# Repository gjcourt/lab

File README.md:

<!-- readme-type: content -->

# lab

A curated list of 140 multidisciplinary engineering and skill-building projects

Picking a next project to learn on tends to default to whatever's easiest, not to whatever actually
builds a skill that's missing. `lab` (formerly `brainstorm`) tracks 140 project briefs spanning
software, hardware, woodworking, finance, and music, each one scoped and leveled against existing
skills (Go, Kubernetes, Docker) so the next pick is deliberate rather than convenient. It's a
personal planning catalog, not a set of finished write-ups — most entries are still `Not Started`.

**Status:** active — 140 briefs (1 done, 17 in progress), last content update 2026-10-08; the
espresso profiling build is installed on the machine and its controller app, Vibrato, runs in the
homelab (see [`06-coffee-espresso/AGENTS.md`](06-coffee-espresso/AGENTS.md)).

## Layout

Each directory holds one Markdown file per project plus a `projects.md` index; three also carry a
`_reference/` directory with as-built notes for the work that's actually underway.

```text
01-audio-midi/          22 projects — DSP, custom controllers, and audio hardware
02-woodworking/         15 projects — functional furniture, speaker cabinets, homelab enclosures
03-homelab-automation/  43 projects — eBPF, K8s operators, ESP32 sensors, and infrastructure
04-finance-analysis/    16 projects — EDGAR parsing, DCF modeling, personal finance tracking
05-piano/               15 projects — classical repertoire tools, jazz theory, improvisation
06-coffee-espresso/     19 projects — Lucca A53 profiling, leva! firmware, sensor integration
07-cross-disciplinary/  10 projects — projects blending multiple categories
```

## Conventions

Each project is one file, `NN-NNN-slug.md`, inside its category directory, where `NN` matches the
directory prefix. Every file starts with YAML frontmatter:

```yaml
---
title: 'ESP32 I2S DAC Streamer'
number: '01-001'
category: 'audio-midi'
difficulty: 'Medium'
time_commitment: '1-4 weeks'
target_skills: 'C++, ESP-IDF, I2S, Audio Streaming'
status: 'Not Started'
depends_on: # optional
  - hardware/esp32
---
```

`difficulty` is `Easy` (1-2 days, builds on existing skills), `Medium` (1-4 weeks, combines
disciplines or introduces new concepts), or `Hard` (months, stretches into low-level domains such as
C/C++, RTOS, or advanced finance/music theory). `status` moves from `Not Started` through
`In Progress` to `Done`, or ends at `Cancelled` when a project is dropped. `depends_on` points at a
prerequisite — another project's `NN-NNN`, or a resource reference like `hardware/esp32`. Every file
also needs an `## Exit Criteria` section.

To add a project, create the file with this frontmatter in the right category directory and update
that category's `projects.md` count. To renumber prefixes after reordering, run
`python update_prefixes.py`. See [`AGENTS.md`](AGENTS.md) for the validation commands CI runs on
every change.

## License

No licence file yet.

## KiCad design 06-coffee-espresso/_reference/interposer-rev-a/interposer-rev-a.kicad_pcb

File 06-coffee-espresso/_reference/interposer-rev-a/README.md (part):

# Unified ESP32 interposer, rev A: schematic

The schematic for [06-014](../../06-014-unified-esp32-interposer-board.md), drawn before George's
measurements M1–M10 came in and updated on 2026-11-08 with the ones he took that day (bench page
Tests 28–37, one per M; cited as **Test n**). The design of record is the
[rev A plan](../../../docs/plans/2026-10-27-unified-esp32-interposer-rev-a-plan.md) (cited as **plan
§n**). The 06-015 flow tap it absorbs is in [`../flow-tap-pcb/`](../flow-tap-pcb/README.md).

**Status (2026-11-08): schematic as data, ERC-clean; draft layout, DRC-clean, not ready to order**
(see [Layout](#layout-draft-2026-11-08) and its
[not ready to order until](#not-ready-to-order-until) list). M1, M6, M7 and M9 are closed; M2 is
closed to "EXCON 2547, probable" (caliper check pending); M3 has its resistance half and George's
front-end decision but no live node voltages; M10 has the mount sites but no cable lengths. Nothing
here is a guess. Every value that waits on a measurement is listed in
[Placeholders](#placeholders-what-closes-each-one), and every part number comes from a datasheet or
a JLCPCB part page read on 2026-10-28 (no new LCSC numbers were added on 2026-11-08).

| File                                                 | What it is                                                                                                   |
| ---------------------------------------------------- | ------------------------------------------------------------------------------------------------------------ |
| [`circuit.py`](circuit.py)                           | **Single source of truth.** Parts, nets, NC pads, GPIO map, placeholders. Importable by a future generator.  |
| [`check_circuit.py`](check_circuit.py)               | ERC-style checker (11 checks). Exit 0 = pass.                                                                |
| [`footprints/`](footprints/)                         | The 26 footprints `circuit.py` names (24 KiCad 9 library, 2 EXCON authored) + 2 layout-only (hole, test pad) |
| [`gen_excon_footprints.py`](gen_excon_footprints.py) | Writes `EXCON_2547-02_WV` / `-04_WV` from EXCON drawing C2547WV rev E. Plain Python.                         |
| [`generate_pcb.py`](generate_pcb.py)                 | Layout generator (KiCad 9 `pcbnew` API): reads `circuit.py`, writes the board, BOM and CPL.                  |
| `interposer-rev-a.kicad_*`, `fp-lib-table`           | The generated KiCad project (board, netclasses, custom DRC rule, library table pointing at `footprints/`).   |
| [`routing/`](routing/)                               | The Freerouting session the board is built from (committed, so regeneration doesn't need the router).        |
| [`fab/`](fab/)                                       | Gerber + drill zip, JLC BOM + CPL, assembly drawing (PDF), top/bottom renders, DRC report.                   |

```sh
cd 06-coffee-espresso/_reference/interposer-rev-a
python3 circuit.py              # part / net summary per function block
python3 check_circuit.py -v     # ERC; -v also prints the GPIO map
```

Output today: `116 parts (74 fitted, 42 DNP), 86 nets` and `ALL 11 CHECKS PASS`. Plain Python 3, no
dependencies. The checker reads pad names straight out of the vendored `.kicad_mod` files, so a typo
in a pin number fails C1.

**No KiCad schematic (`.kicad_sch`) in this rev.** kiutils can write one, but every one of the 105
parts would need a library symbol placed and wired or labelled by hand-written coordinates, and
`kicad-cli` has no headless netlist import to validate a `.net` file against. That is hours for a
drawing that adds nothing `circuit.py` + the checker don't already enforce. The layout generator
should read `circuit.py` directly (as 06-015's `generate_pcb.py` hard-codes its nets today), and DRC
on the generated board is the KiCad-side validation.

## What the checker enforces

| #   | Rule                                                                                                                                                                                           | Source                      |
| --- | ---------------------------------------------------------------------------------------------------------------------------------------------------------------------------------------------- | --------------------------- |
| C1  | Every part has a vendored footprint; every `REF.pad` named exists in it                                                                                                                        | KiCad 9 library             |
| C2  | Every footprint pad is on a net or listed in `NC` with a reason                                                                                                                                | —                           |
| C3  | Every net ≥ 2 pins; no pin on two nets                                                                                                                                                         | —                           |
| C4  | GICAR meter supply (`N_PLUS`; ~3.3 V measured, Test 36) touches only `J1.2` / `J2.2`                                                                                                           | 06-015, plan §3.4           |
| C5  | ito 5 V (`V5_ITO`, `ITO_EXP_5V`) never meets `+3V3` / `+5V` / `VBUS`, directly or through any R, C, D, jumper or switch; U1 on ito 5 V, U2 on 3V3                                              | plan §3.4                   |
| C6  | Each GPIO used once and matches the GPIO table; no strapping, octal-PSRAM, UART0 or non-existent pin; USB only on GPIO19/20; analog nets on ADC1                                               | ESP32-S3-WROOM-1 DS v1.8    |
| C7  | `SB` / `SL` probe lines touch only the pass-through connectors and the series coupling cap; the aux pins are pure pass-through                                                                 | plan §3.3                   |
| C8  | `S1` / `S2` feeds touch only the pass-through connectors and one series R into a follower; the follower input has only a BAV99 to +5V / GND; the divider holds the ADS input under VDD + 0.3 V | plan §3.2, SBAS444E         |
| C9  | `ENC` lines touch only connectors, FET drains (source on GND, gate pulled down) and LVC inputs: pull-low only, never driven high. J14.1 NC, J15.1 GND                                          | plan §3.5, Test 33          |
| C10 | IC power pins on the intended rails                                                                                                                                                            | each datasheet's pin table  |
| C11 | M9 tap: U13's line pins, its RX output and the passive path reach M9 / GPIO38 only through DNP links; DIN1 has its pull-up                                                                     | George 2026-11-08, SLLS410O |

The checker was mutation-tested: putting a part on `N_PLUS`, a resistor on `SB_PROBE`, a pull-up on
`ENC_A`, GPIO3 on a signal, or `R39` from `V5_ITO` to 3V3 each fails the right check. On 2026-11-08:
a part on `S1_FEED`, a clamp off its rail, and a GND on `J14.1` each fail too.

## Blocks

Pass-through copper is drawn `═══`. Every machine signal goes in on one connector and straight out
on its mate. Only `ENC` can pull low (plan §2 design invariant).

### F0 power, ESP32, USB

```text
 J4 XH-2 (5V in, our choice: 1 = +5V, 2 = GND) ──────────────┬── +5V ──┬── U6 VDD (NTC followers)
                                                             │         │
 J5 USB-C ── VBUS ──►|── D1 SS34 (VBUS → +5V only) ──────────┘   C3 10µ│
   CC1 ── R1 5k1 ── GND     CC2 ── R2 5k1 ── GND                       │
   D+ (A6,B6) ══ U3 USBLC6-2SC6 (1/6) ══ GPIO20                 U4 AMS1117-3.3 (VIN 3, GND 1, VOUT 2/tab)
   D- (A7,B7) ══ U3 (3/4) ═════════════ GPIO19                         │
   U3.5 VBUS, U3.2 GND                                         +3V3 ──┴── C4 22µ ── U5.2 3V3 (C5 22µ + C6 100n at pin)
 U5 ESP32-S3-WROOM-1-N8:  EN ── R3 10k ── 3V3, C7 1µ ── GND, SW1 ── GND   (DS v1.8 §9: R = 10k, C = 1µF)
                          GPIO0 ── R4 10k ── 3V3, SW2 (BOOT) ── GND
```

- **Never plug USB in while the machine is plugged in** (plan §3.1). D1 only stops the 5 V PSU
  back-feeding a USB host. It is not isolation.
- **The board's GND is chassis earth once installed.** The control board's GND is isolated from
  mains (Test 28: GND to N and to F open unplugged; GND to PE 2 mV AC, 0 V DC powered; PS1 is a
  Lauma SMR30.10, Class II), but it is bonded to the chassis through M3 pin 4, the steam-level
  return to the boiler body (Test 30: GND to the earth screw beeps with M3 plugged in, not with it
  out). So flash an installed board from a grounded or battery-powered laptop.
- **USB headroom:** AMS1117 dropout is 1.3 V max at 0.8 A, so it wants ≥ 4.6 V in. USB through D1
  can sit just under that. Flashing works; Wi-Fi TX peaks on USB power may brown out. Use J4 for
  bench tests T2+.

### F1 / F2 `S1` / `S2` NTC taps (one follower per feed)

The control board's sensor headers (Test 29, George's trace on his v.05.01 board): **M2** 2-pin =
steam NTC (`S1`), 1 GND, 2 feed. **M3** 4-pin = 1 GND, 2 group NTC feed (`S2`), 3 steam-boiler level
probe (`SB`), 4 GND (the level return, wired to the boiler body). So `S2` and `SB` share one plug,
and J8/J9 carry both.

```text
 J6.2 (S1 steam probe) ═══════ S1_FEED ═══════ J7.2 (→ control board M2.2)
 J6.1 / J7.1 = GND (Test 30: 0.2 Ω to M6 pin 3)  ── tied to the board GND
                                │
                               R5 1M                       (George 2026-11-08: "1 MΩ series")
                                │  S1_IN ── D2 BAV99 to +5V / GND
                       U6A MCP6004 follower (IN+ 3, IN- 2 = OUT 1), VDD = +5V
                                │  S1_BUF
                               R9 10k ── S1_ADC ── R13 5.1k ── GND, C9 100n ── GND
                                │
                           U7 ADS1115 AIN0          S2: J8.2/J9.2, R6, D3, U6B, R10/R14, C10 → AIN1
 U7: VDD 3V3 (C13 100n), ADDR = GND → 0x48, AIN2/AIN3 = GND (unused), ALERT/RDY → R21 10k ── 3V3, GPIO10
 U6C / U6D unused: OUT tied to IN-, IN+ at GND
```

- **George's decisions (2026-11-08).** First: "Measure 0–5.5 V, survive 24 V", a high-impedance
  buffered input with series R plus clamp diodes so up to ~24 V can't damage it, without loading the
  probe (the control board must read the same temperature). Then, answering the two questions this
  raised: **"1 MΩ series"** and **"Accept 0–5.0 V"**.
- **Only the feed is buffered.** Test 30 found pin 1 of each probe header at GND (0.2 Ω) and pin 2
  the feed, so the second follower per probe that rev A drew "in case the GND pin is the other one"
  is gone, and the NTC GND pins join the board GND.
- **Range: 0 to ~5.0 V.** U6 stays on +5V. The MCP6004 is rail-to-rail: its input range ends at
  VDD + 0.3 V and its output at VDD − 25 mV (DS20001733L), so it reads 0 to ~5.0 V. That covers the
  1.5–4.7 V estimate below. Revisit in rev B if the live measurement shows the node near 5 V.
- **Divider after the follower, unchanged.** R9/R13 = 10k/5.1k = 0.338: 5.0 V at the node is 1.69 V
  at the ADS, 83 % of the ±2.048 V FSR, ~185 µV per code at the node. A closer ratio would need a
  new resistor value for less than one bit, so it stays. The follower output can't exceed +5V, so
  the ADS pin stays under VDD + 0.3 V (SBAS444E abs max; checker C8). The divider loads the op-amp,
  never the node.
- **Series R = 1 MΩ.** A 24 V fault pushes (24 − 5.3) V / 1 MΩ = 19 µA into D2 and the op-amp input
  diodes, against the MCP6004's ±2 mA input-pin rating (checker C8 recomputes this). With the
  interposer **unpowered** and the machine on, the feed reaches the dead +5V rail through 1 MΩ and
  the clamp: with the 5 V / 15 kΩ model at 94 °C that is ~1.7 µA, ~12 mV at the group node, about
  0.3 °C at the control board (100 kΩ would have been ~3 °C). **Test T4 runs with the interposer
  powered and unpowered.**
- **D2/D3 fitted, with a cost to watch.** BAV99 leakage is ≤ 25 nA at 20 V (Diodes ds12007). Through
  1 MΩ that is ≤ 25 mV worst case at the follower (~0.6 °C at 94 °C), and ≤ 0.4 mV at the node
  through the ~15 kΩ feed, so it costs reading accuracy, not control-board accuracy. If T3 shows it
  matters, D2/D3 can go DNP: the op-amp's own input diodes and 1 MΩ still hold a 24 V fault to 19
  µA.
- **Node estimate (Test 30, not yet measured live):** feed pin to GND reads 15 kΩ (M3) and 16.5 kΩ
  (M2) on the unpowered board, so assuming 5 V through ~15 kΩ: group ~4.7 V cold and ~2.4 V at 94
  °C, steam ~4.6 V cold and ~1.5 V at 6.8 kΩ. The live check waits for an EXCON extension lead.
- **Curves (firmware, Test 30):** group 249 kΩ at 21 °C and 13.3 kΩ at 94 °C, so β ≈ 4340 K, R25 ≈
  205 kΩ. Steam 201.7 kΩ at 21 °C and 6.8 kΩ hot at an unknown temperature: it needs a second known
  point.

### F3 / F4 `SB` / `SL` level taps (pass-through + DNP AC front-end)

```text
 J8.3 (SB probe, M3 pin 3) ═════ SB_PROBE ═════ J9.3     J8.4 ═════ SB_AUX (level return) ═════ J9.4
                           │                                (pure pass-through: not tied to our GND)
                        C14 (DNP, series coupling C; value + voltage TBD at M4)
                           │  SB_AC
                        R22 100k (DNP)
                           │  SB_FE ── R24 1M ── 3V3, R26 1M ── GND (DNP mid-rail bias)
                           │         D6 BAV99 (DNP) to 3V3 / GND
                         GPIO1 (ADC1_CH0)          SL: J12/J13 (M10), C15, R23, R25, R27, D7 → GPIO2 (ADC1_CH1)
```

- The probe line touches **only** the connectors and C14 (checker C7). The bias sits on our side of
  the capacitor, so no DC ever reaches the probe (plan §3.3).
- The level return (M3 pin 4) is GND on the control board (0.9 Ω, Test 30) and runs to the boiler
  body. It is kept pure pass-through here so the probe's current never runs through our ground
  plane.
- Firmware samples the AC amplitude on ADC1. ADC1 is used because ADC2 can't run alongside Wi-Fi
  (ESP32-S3 Series DS v2.2).
- Everything after the connectors is DNP until M4/M5 (Tests 31/32 not done). `SL` is M10, a 2-pin
  EXCON header (Test 29); which pin is signal and which is return is unknown, so pin 1 is drawn as
  the tapped line and pin 2 is passed through and touches nothing else.

### F5 flow: 06-015 circuit + ESP32 buffer

```text
 J1 GICAR (EXCON 2547-4)                           J2 to control board M6 (EXCON 2547-4)
   1 key-blank                                       1 key-blank
   2 + ~3.3V ══════════ N_PLUS ═══════════════════   2     (J1.2 ↔ J2.2 ONLY; checker C4)
   3 GND    ═══════════ GND ══════════════════════   3
   4 o      ═══════════ N_O ══════════════════════   4
                         ├── U1 74LVC1G17 @ ito 5V (VCC 5 = J3.3 V5_ITO, C1 100n) ── Y 4 ── J3.2 → ito IMPULSE
                         └── U2 74LVC1G17 @ 3V3 (C2 100n) ── Y 4 ── FLOW_3V3 ── GPIO11 (pulse_counter)
 J3 to ito (XH-3): 1 GND, 2 OUT, 3 +5V (ito's)
```

- J3/U1/C1 and the net names are 06-015's, unchanged. **J1/J2 change family:** M6 is the same black
  EXCON 2547 header as the sensor headers (Test 29), not JST XH, so the 06-015 XH pair does not mate
  with this machine.
- **The meter supply is ~3.3 V here, not 14.3 V** (Test 36, meter unplugged: P2→P3 3.3 V, P4→P3 4.9
  V, P2→P4 1.62 V; P2 red, P3 black, P4 white, P1 the blank key). The 14.3 V figure came from a
  forum thread, never this machine. Everything on M6 is ≤ 5 V. The pass-through-only rule (checker
  C4) stays: it is the meter's own supply. The loaded supply voltage (meter connected) waits for an
  EXCON extension lead.
- **The plan's "confirm at layout" is closed:** SN74LVC1G17 input range is 0–5.5 V at any VCC
  (SCES351Y, recommended operating conditions), so U2 takes the 4.9 V `o` while powered from 3.3 V.
  Ioff keeps both buffers from loading `o` when their supply is off.
- ito's 5 V (`V5_ITO`) and our `+3V3` / `+5V` share only GND (checker C5).

### F6 ito `ENC` interposer (3 lines: SW, A, B)

```text
 J14 KK-4 (encoder cable)  1 empty (NC)          1 GND ═══ J15 KK-4 (to ito ENC)
                           2 SW  ═══ ENC_SW ═══ 2 ── Q3 drain │ U10 A
                           3 A   ═══ ENC_A ════ 3 ── Q1 drain │ U8 A
                           4 B   ═══ ENC_B ════ 4 ── Q2 drain │ U9 A
 inject:  GPIO4/5/6 ── R28-30 1k ── gate Q1-3 AO3400A (source GND) ; gate ── R31-33 100k ── GND
 read:    U8/U9/U10 74LVC1G17 @ 3V3 (C16-18 100n), Y → GPIO7 / GPIO15 / GPIO16
```

- **Three lines.** The encoder sits on the display board (V1.3), and its cable carries only SW / A /
  B in holes 2 / 3 / 4; hole 1 is empty, because the display board gets GND over the SPI cable (Test
  33). Each line passes a 4.7 kΩ series resistor on the display board (R1–R3, with C5–C7 on the
  encoder side). ito's ENC pin 1 is GND, so J15.1 carries our GND to ito as the FETs' return, and
  J14.1 is NC (checker C9). The order matches the ito manual (p.63) and the KK 254 2.54 mm family
  (Test 33: ~7.7 mm across 4 pins).
- **Idle high, pull-low only** (Test 34, in the machine): SW, A and B rest at 5.05 V (ito pull-ups),
  A and B are open at the detents tried, SW pressed reads 0 V. Nothing needs masking at rest.
  Pulling a line low on the ito side drives the ito input directly and sees the encoder's caps only
  through 4.7 kΩ.
- **Pull-low only:** the FET can only short a line to GND, like a detent closing, and nothing ever
  drives a line high (checker C9). The 100 kΩ gate pull-downs hold every FET off while the ESP32 is
  unpowered, in reset, or booting, so the knob behaves stock.
- AO3400A: Vgs(th) 0.65–1.45 V, Rds(on) < 48 mΩ at Vgs 2.5 V (AOS DS rev 3.1), so a 3.3 V GPIO turns
  it fully on. Pinout 1 G, 2 S, 3 D. It is a JLC basic part, so no loading fee. The plan's other
  option, a 74LVC1G07, idles low with its input low, which would inject at boot.
- Read-back is a 5 V-tolerant LVC Schmitt input (II ±5 µA max), not a divider, so it adds no DC load
  to ito's pull-ups.

### F7 shared I²C

```text
 GPIO8 SDA / GPIO9 SCL ── R34 / R35 4.7k ── 3V3
   ├── U7 ADS1115 (0x48)
   ├── J16 Qwiic JST-SH 4-pin: 1 GND, 2 3V3, 3 SDA, 4 SCL (sparkfun.com/qwiic)
   └── U11 PCA9306 (DNP): VREF1 = 3V3, SCL1/SDA1 = bus; VREF2 = EN ── R36 200k (DNP) ── ito 5V
         SDA2 ── JP2 (open) ── J17.5 EXP SDA      SCL2 ── JP3 (open) ── J17.4 EXP SCK
         R37 / R38 4.7k (DNP) SDA2/SCL2 ── ito 5V       J17 (DNP): 1 +5V(ito), 2 GND, 3 NC, 4 SCK, 5 SDA
```

- PCA9306 hookup per SCPS113O §8.1.2 (EN tied to VREF2, 200 kΩ to the high-side supply). VREF1 ≤
  VREF2 − 0.6 V is satisfied by 3.3 V / 5 V.
- JP2/JP3 open and U11 unfitted mean the ito `EXPANSION` bus is isolated by default. There is no
  multi-master in rev A (plan §3.6).

### F8 `SER` stub (all DNP)

```text
 J18 (1x6 0.1"): 1 GND, 2 SER_3V3_H ── R39 0R ── 3V3,
   3 SER_TX_H ── R40 ── SER_TX ── GPIO17 (U1TXD)     each MCU-side net also has a DNP divider-bottom
   4 SER_RX_H ── R41 ── SER_RX ── GPIO18 (U1RXD)     R (R44-R47) to GND and a DNP BAV99 clamp
   5 SER_IO1_H ── R42 ── SER_IO1 ── GPIO13            (D8-D11) to 3V3 / GND
   6 SER_IO2_H ── R43 ── SER_IO2 ── GPIO14
```

Values are TBD until the M8 / Saleae capture. Nothing is inserted into the touchpad link (plan
§3.7).

### F8b control-board M9 "RS232 serial" tap

M9 is a 4-pin EXCON header on the control board with nothing plugged in. The case sticker labels it
"RS232 serial / Seriale 232" (Test 29). Its pin roles and levels are unknown: **scope before
connecting.** Two paths to UART2 are drawn; **every connection from either path to M9 is an open DNP
link**, so nothing touches the machine until M9 is scoped and one path is chosen.

```text
 J20 EXCON 2547-4 (DNP, cable to M9) pins 1..4 ══ M9_P1..P4 ══ J21 (1x6 0.1", DNP) pins 1..4

 transceiver path (U13 fitted, links DNP):
   GPIO21 (UART2 TX) ── M9_TX ── U13 DIN1 (11)      R55 10k ── 3V3 (pull-up, fitted)
   U13 DOUT1 (14) ── R52 0R (DNP) ── J22.1 ;  J22.2 ── R53 0R (DNP) ── U13 RIN1 (13)
   U13 ROUT1 (12) ── R54 0R (DNP) ── M9_RX ── GPIO38 (UART2 RX)
   U13 MAX3232 @ 3V3: C19 C1+/C1-, C20 C2+/C2-, C21 V+→GND, C22 GND→V-, C23 VCC bypass (all 0.1 µF)
   channel 2: DIN2 (10) = GND, DOUT2 / RIN2 / ROUT2 unconnected

 passive path (all DNP):
   GPIO21 ── R49 (TBD) ── M9_TX_H ── J21.5
   GPIO38 ── M9_RX ── R50 (TBD) ── M9_RX_H ── J21.6 ;  M9_RX: R51 (TBD) ── GND, D12 BAV99 to 3V3 / GND
```

- **George 2026-11-08:** "Add a DNP transceiver footprint", then "why wouldn't we place the
  transceiver if it's cheap?". So U13 and its caps are **fitted**, and only the links are DNP.
- **Why the links stay open:** the MAX3232's driver swings about ±5.4 V (VOH/VOL at 3 kΩ, TI
  SLLS410O §6.6). If M9 is 5 V logic into the control board's MCU, that could damage the machine.
  Scope M9 first, then fit **one** path: R52 + R53 + R54 for the transceiver, or R49–R51 + D12 for
  logic levels, plus two wire links from the M9 pins on J21.1–4 to J22.1/.2 or J21.5/.6. Checker C11
  fails if any part on those nets is fitted.
- **RS-232 is inverted vs TTL** (a mark is the negative level). The MAX3232 inverts back; on the
  passive path, the ESP32 UART can invert in software if M9 turns out to be inverted logic.
- **Nothing on the ESP32 side can back-drive the machine with the links open.** GPIO21 drives only
  U13 DIN1 (a logic input, ±1 µA, SLLS410O §6.6) and the open R49. U13's line outputs end at open
  R52/R53. GPIO38 sees nothing until R54 or R50 is fitted.
- **One pull-up, one not.** DIN1 gets R55 10k to 3V3 (fitted): the datasheet says every DIN must sit
  at a valid low or high (§8.3.2, §9.2.2) and DIN has no internal pull (input current ±1 µA), while
  GPIO21 is unconfigured at boot. High is UART idle (mark). GPIO38 gets no external resistor:
  floating, it is an unconfigured ESP32 input that drives nothing, and once a path is fitted it is
  driven (ROUT1 is push-pull; an open RIN reads as a high ROUT, §8.3.3). Firmware can enable the
  internal pull-up.
- **U13:** TI MAX3232EIDR, SOIC-16, LCSC C193666 (JLC extended, read 2026-11-08), 3–5.5 V, 250
  kbit/s, ±15 kV ESD on the line pins. Caps 0.1 µF each at VCC 3.3 V (Table 9-1); C3 may go to VCC
  or GND (Fig 9-1); the 50 V 0603 X7R part covers V+/V− (≤ 7 V abs max).
- UART2 reaches GPIO21/38 through the GPIO matrix. Both were spare.

### F9 on/off dry contact (all DNP)

```text
 GPIO12 ── R48 330 (DNP) ── U12 TLP222A pin 1 (LED A), pin 2 (LED K) ── GND
 U12 pins 4 / 3 (contact) ── J19 pins 1 / 2 (to the panel ON/OFF pair, if M8 finds one)
```

The TLP222A datasheet could not be retrieved, so the pinout and the LED resistor are **unverified**.
Check both against the datasheet before fitting.

## GPIO allocation

ESP32-S3-WROOM-1 module pins from datasheet v1.8 Table 3-1. Checker C6 enforces every row.

| GPIO | Module pin | Net          | Use                                  |
| ---- | ---------- | ------------ | ------------------------------------ |
| 0    | 27         | `BOOT`       | strapping (boot mode): SW2 + R4 only |
| 1    | 39         | `SB_FE`      | ADC1_CH0, SB level (DNP until M4)    |
| 2    | 38         | `SL_FE`      | ADC1_CH1, SL level (DNP until M5)    |
| 4    | 4          | `ENC_INJ_A`  | Q1 gate (pull `ENC_A` low)           |
| 5    | 5          | `ENC_INJ_B`  | Q2 gate                              |
| 6    | 6          | `ENC_INJ_SW` | Q3 gate                              |
| 7    | 7          | `ENC_RD_A`   | U8 read-back                         |
| 8    | 12         | `I2C_SDA`    | ADS1115, Qwiic, (PCA9306)            |
| 9    | 17         | `I2C_SCL`    |                                      |
| 10   | 18         | `ADS_ALERT`  | ADS1115 ALERT/RDY                    |
| 11   | 19         | `FLOW_3V3`   | flow `pulse_counter` (U2)            |
| 12   | 20         | `ONOFF_DRV`  | F9 photorelay LED (DNP)              |
| 13   | 21         | `SER_IO1`    | F8 spare (DNP)                       |
| 14   | 22         | `SER_IO2`    | F8 spare (DNP)                       |
| 15   | 8          | `ENC_RD_B`   | U9 read-back                         |
| 16   | 9          | `ENC_RD_SW`  | U10 read-back                        |
| 17   | 10         | `SER_TX`     | U1TXD, F8 (DNP)                      |
| 18   | 11         | `SER_RX`     | U1RXD, F8 (DNP)                      |
| 19   | 13         | `USB_DN`     | USB D- (fixed)                       |
| 20   | 14         | `USB_DP`     | USB D+ (fixed)                       |
| 21   | 23         | `M9_TX`      | UART2 TX → U13 DIN1 (R55 pull-up)    |
| 38   | 31         | `M9_RX`      | UART2 RX ← R54 or R50 (DNP links)    |

Deliberately unused: GPIO3, 45, 46 (strapping, left at their datasheet defaults, Table 4-1);
GPIO35–37 (octal PSRAM on R8 modules, Table 3-1 note b, kept free so a module swap is safe);
GPIO43/44 (UART0 ROM console; add test pads at layout); GPIO39–42 (JTAG, spare); GPIO47, 48 (spare).
GPIO26–34 are not module pins.

## Power budget

| Load                       | Rail   | Current                         | Source                   |
| -------------------------- | ------ | ------------------------------- | ------------------------ |
| ESP32-S3-WROOM-1 Wi-Fi TX  | 3V3    | 355 mA peak (802.11b, 20.5 dBm) | module DS v1.8 Table 6-4 |
| ESP32 supply requirement   | 3V3    | **≥ 0.5 A** must be available   | module DS v1.8 Table 6-2 |
| ADS1115                    | 3V3    | 0.2 mA max (25 °C), 0.3 mA max  | SBAS444E §5.5            |
| MCP6004 (4 amps)           | 5V     | 4 × 170 µA max = 0.68 mA        | DS20001733L              |
| S1/S2 dividers (15.1 kΩ)   | 5V     | ≤ 2 × 0.33 mA (via U6)          | Ohm's law                |
| 74LVC1G17 × 4 (U2, U8–U10) | 3V3    | 4 × 10 µA max                   | SCES351Y ICC             |
| I²C pull-ups (both low)    | 3V3    | 2 × 0.7 mA                      | Ohm's law, 4.7 kΩ        |
| AMS1117 quiescent          | 5V     | 11 mA max                       | AMS1117 DS               |
| U1 74LVC1G17 (ito domain)  | ito 5V | 10 µA max (from ito, as 06-015) | SCES351Y                 |

- **Design point:** 3V3 at 0.5 A (the module's own requirement dominates; everything else is < 5
  mA). 5 V input ≥ 0.52 A (about 2.6 W). Spec the off-board PSU for ≥ 1 A at 5 V. ito's own HLK-PM01
  is only documented as "5 V ≥ 600 mA" (ito manual p.70), which leaves thin margin. A dedicated
  module or a 1 A+ USB brick is the safer choice.
- **LDO heat:** (5.0 − 3.3) V × 0.355 A = 0.60 W at the TX peak. SOT-223 θJA is 90 °C/W (AMS DS), so
  a sustained peak would be a 54 °C rise. TX is bursty, so the average is far lower. Give the tab a
  copper pour at layout anyway, and measure the rail during T2.

## BoM

From `circuit.py` (it is the source; regenerate rather than hand-edit). Library class is as read on
each **jlcpcb.com/partdetail** page on 2026-10-28. **Stock is unchecked for every part**: the page
text we could read shows no stock figure. Check all of it on order day (plan §6). "unstated" means
the page showed no clear Basic/Extended label.

| Refs                        | Value                       | MPN                       | LCSC     | JLC class   | Fit |
| --------------------------- | --------------------------- | ------------------------- | -------- | ----------- | --- |
| U5                          | ESP32-S3-WROOM-1-N8         | Espressif                 | C2913198 | extended    | fit |
| U4                          | AMS1117-3.3, 1 A            | AMS1117-3.3               | C6186    | basic       | fit |
| U6                          | MCP6004 quad op-amp         | MCP6004T-I/SL (Microchip) | C7378    | extended    | fit |
| U7                          | ADS1115                     | ADS1115IDGSR (TI)         | C37593   | extended    | fit |
| U1 U2 U8 U9 U10             | 74LVC1G17                   | SN74LVC1G17DBVR (TI)      | C7836    | extended    | fit |
| Q1 Q2 Q3                    | AO3400A N-FET               | AO3400A (AOS)             | C20917   | basic       | fit |
| U3                          | USB ESD                     | USBLC6-2SC6 (ST)          | C7519    | extended    | fit |
| J5                          | USB-C 16P                   | TYPE-C-31-M-12 (HRO)      | C165948  | extended    | fit |
| D1                          | Schottky 3 A 40 V           | SS34 (MDD)                | C8678    | unstated    | fit |
| D2 D3                       | BAV99                       | BAV99,215 (Nexperia)      | C2500    | unstated    | fit |
| J16                         | JST-SH 4-pin (Qwiic)        | SM04B-SRSS-TB(LF)(SN)     | C160404  | extended    | fit |
| SW1 SW2                     | tactile 5.1 mm              | TS-1187A-B-A-B (XKB)      | C318884  | unstated    | fit |
| C1 C2 C6 C8–C10 C13 C16–C18 | 100 nF 50 V X7R 0603        | CC0603KRX7R9BB104         | C14663   | basic       | fit |
| C7                          | 1 µF 0603                   | CL10A105KB8NNNC           | C15849   | basic       | fit |
| C3                          | 10 µF 0805                  | CL21A106KAYNNNE           | C15850   | basic       | fit |
| C4 C5                       | 22 µF 0805                  | CL21A226MAQNNNE           | C45783   | unstated    | fit |
| R28–R30                     | 1 kΩ                        | 0603WAF1001T5E            | C21190   | basic       | fit |
| R34 R35                     | 4.7 kΩ                      | 0603WAF4701T5E            | C23162   | basic       | fit |
| R1 R2 R13 R14               | 5.1 kΩ                      | 0603WAF5101T5E            | C23186   | basic       | fit |
| R3 R4 R9 R10 R21            | 10 kΩ                       | 0603WAF1002T5E            | C25804   | basic       | fit |
| R31–R33                     | 100 kΩ                      | 0603WAF1003T5E            | C25803   | basic       | fit |
| R5 R6                       | 1 MΩ                        | 0603WAF1004T5E            | C22935   | basic       | fit |
| U13                         | MAX3232 RS-232              | MAX3232EIDR (TI)          | C193666  | extended    | fit |
| C19–C23                     | 100 nF 50 V X7R 0603        | CC0603KRX7R9BB104         | C14663   | basic       | fit |
| R55                         | 10 kΩ                       | 0603WAF1002T5E            | C25804   | basic       | fit |
| R52–R54                     | 0 Ω (links)                 | 0603WAF0000T5E            | C21189   | basic       | DNP |
| D6–D12                      | BAV99                       | BAV99,215 (Nexperia)      | C2500    | unstated    | DNP |
| U11                         | PCA9306                     | PCA9306DCUR (TI)          | C33196   | extended    | DNP |
| U12                         | TLP222A photorelay          | TLP222A(TP1,F) (Toshiba)  | C2152279 | extended    | DNP |
| C14 C15                     | 100 nF (TBD at M4/5)        | CC0603KRX7R9BB104         | C14663   | basic       | DNP |
| R22 R23                     | 100 kΩ                      | 0603WAF1003T5E            | C25803   | basic       | DNP |
| R24–R27                     | 1 MΩ                        | 0603WAF1004T5E            | C22935   | basic       | DNP |
| R36                         | 200 kΩ                      | 0603WAF2003T5E            | C25811   | basic       | DNP |
| R37 R38                     | 4.7 kΩ                      | 0603WAF4701T5E            | C23162   | basic       | DNP |
| R39                         | 0 Ω                         | 0603WAF0000T5E            | C21189   | basic       | DNP |
| R48                         | 330 Ω (TBD)                 | 0603WAF3300T5E            | C23138   | basic       | DNP |
| R40–R47 R49–R51             | TBD                         | —                         | —        | —           | DNP |
| J1 J2 J8 J9                 | EXCON 2547 4-pin            | 254704WV203 (probable)    | —        | hand-solder | fit |
| J6 J7 J12 J13               | EXCON 2547 2-pin            | 254702WV203 (probable)    | —        | hand-solder | fit |
| J20                         | EXCON 2547 4-pin            | 254704WV203 (probable)    | —        | hand-solder | DNP |
| J3 / J4                     | JST XH 3 / 2-pin            | B3B / B2B-XH-A            | —        | hand-solder | fit |
| J14 J15                     | Molex KK 254 4-pin          | 22-27-2041                | —        | hand-solder | fit |
| J17 J18 J21 J19 J22         | 1x5 / 1x6 / 1x6 / 1x2 / 1x2 | 2.54 mm header            | —        | hand-solder | DNP |
| JP2, JP3 (open)             | solder jumpers              | copper                    | —        | —           | —   |

**EXCON jumper cables** (one per interposed header, board to control board, plus one for M9 if
fitted): housings 254702HA203 / 254704HA203, terminals 254700TC351 (tin) or 254700TC501 (gold), AWG
26–22 (EXCON 2547HA / 2547TC drawings). Lengths wait on M10. Whether the machine's terminals are tin
or gold is not recorded; match them.

Fitted extended parts (one JLC loading fee each): U5, U6, U7, 74LVC1G17, U3, J5, J16, plus D1, SW
and C4/C5 if their "unstated" class turns out to be extended.

## Placeholders: what closes each one

Closed on 2026-11-08 (George, bench page): **M1** Test 28 (GND isolated from mains; earth-bonded via
M3 pin 4, Test 30), **M6** Test 33 (KK 254, SW/A/B, hole 1 empty, ito pin 1 GND), **M7** Test 34
(idle 5.05 V, A/B open at detents), **M9** Test 36 (meter supply ~3.3 V, `o` 4.9 V).

| Closes     | Refs                                | Placeholder today                                                                                                                                  |
| ---------- | ----------------------------------- | -------------------------------------------------------------------------------------------------------------------------------------------------- |
| **M2**     | J1 J2 J6 J7 J8 J9 J12 J13 J20       | EXCON 2547 is probable (Test 29), not caliper-confirmed: check the 4-pin header is ~12.7 mm wide before ordering housings or boards.               |
| **M3**     | R5 R6 D2 D3 U6 VDD                  | Live node voltages not measured (needs an EXCON extension lead). Range 0 to ~5.0 V ("Accept 0–5.0 V"); revisit in rev B if the node sits near 5 V. |
| **M3**     | R5 R6 D2 D3                         | 1 MΩ ("1 MΩ series"). T4 runs with the interposer powered **and** unpowered. D2/D3 to DNP if T3 shows their leakage matters.                       |
| **M3**     | firmware                            | Steam NTC: 201.7 kΩ at 21 °C, 6.8 kΩ hot at an unknown temperature. Needs a second known point.                                                    |
| **M4**     | C14, R22, R24, R26, D6              | `SB` method + excitation (Test 31 not done). On J8/J9 pin 3; front-end DNP; C14 value/rating TBD.                                                  |
| **M5**     | J12, J13, C15, R23, R25, R27, D7    | `SL` (M10) method and which pin is signal vs return (Test 32 not done). Front-end DNP.                                                             |
| **M8**     | J18, R39–R47, D8–D11, U12, R48, J19 | 16-way ribbon on M1 seen (Test 35, partial); panel end and the ON/OFF pair not reached. All DNP; values TBD.                                       |
| **M9 tap** | J20–J22, R49–R54, D12               | M9 "RS232 serial" pin roles and levels unknown. Scope, then fit ONE path: links R52–R54 (U13) or R49–R51 + D12 (values TBD).                       |
| **M10**    | outline, jumper cables              | Sites measured (Test 37), cable lengths not. See below.                                                                                            |
| DS         | U12, R48                            | TLP222A datasheet not retrieved: pinout and LED current unverified.                                                                                |
| DS         | J17                                 | ito `EXPANSION` pad pitch/form not measured: drawn as a 2.54 mm 1x5 header.                                                                        |
| DS         | U3                                  | USBLC6-2SC6 pinout taken from the KiCad library symbol; the ST datasheet would not download.                                                       |
| DS         | U11                                 | KiCad `VSSOP-8_2.3x2mm` land vs TI DCU land pattern: compare at layout (DNP part).                                                                 |

**M10 mount sites** (Test 37, George): in the control-board box beside M6, 55 × 50 mm, 35 mm deep;
next to the ito on the left side panel, 70 × 50 mm, 25 mm deep; opposite the water tank beside the
vibe pump, about 130 × 120 mm, 30 mm or more deep (heat and pump vibration there). Still to record:
the cable run to each connector and the heat exposure per site.

**Site decision (George, 2026-11-09):** the large bay opposite the water tank, beside the vibe pump
(~130 × 120 mm, ≥30 mm deep): "let's keep it by the water tank / pump so we can fit all the
components. i'd rather have a bigger and more complete board than try to make it fit in a tight
space". The 100 × 60 mm rev A outline stays. Follow-ups for that site: cable runs from there to each
connector (M10), heat exposure near the pump, and vibration-tolerant mounting (standoffs; locking
connectors are already the EXCON/KK families).

## Layout (draft, 2026-11-08)

**100 × 60 mm, 2 layers, 1.6 mm, all SMT on top. DRC: 0 errors, 0 unconnected, 5 warnings** (all
`silk_edge_clearance`: the footprint silk of the USB-C receptacle face and of the module's antenna
end runs to the board edge, where the fab clips it). Report:
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
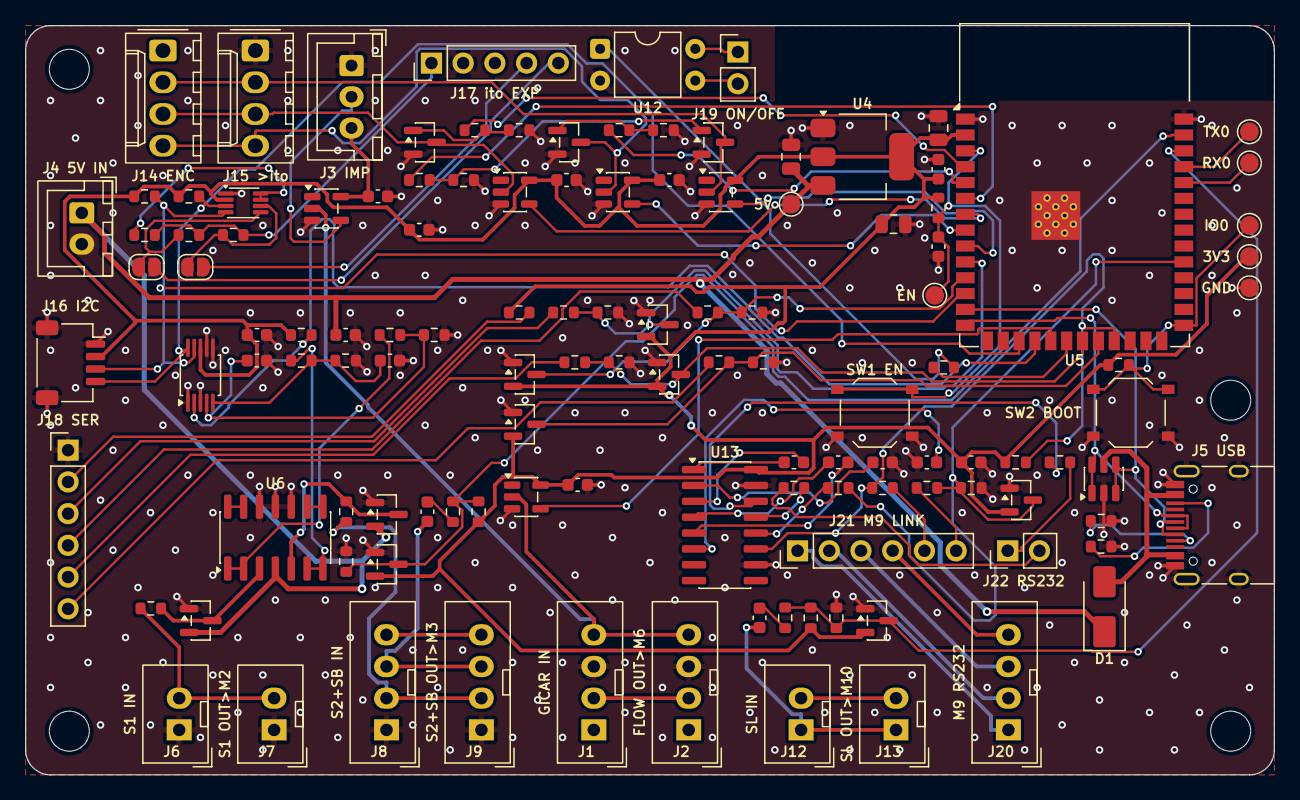
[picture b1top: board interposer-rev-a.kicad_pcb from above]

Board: 2 copper layers, 100.0 x 60.0 mm, 127 parts (0 on the bottom side), 88 nets.

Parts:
C1, C2, C6, C8, C9, C10, C13, C14, C15, C16, C17, C18, C19, C20, C21, C22, C23: 100nF; C_0603_1608Metric
C3: 10uF; C_0805_2012Metric
C4, C5: 22uF; C_0805_2012Metric
C7: 1uF; C_0603_1608Metric
D1: SS34; D_SMA
D2, D3, D6, D7, D8, D9, D10, D11, D12: BAV99; SOT-23
H1, H2, H3, H4: M3; MountingHole_3.2mm_M3
J1: GICAR_meter; EXCON_2547-04_WV
J2: to_Vivaldi (control board M6); EXCON_2547-04_WV
J3: to_ito_IMPULSE; JST_XH_B3B-XH-A_1x03_P2.50mm_Vertical
J4: 5V_IN; JST_XH_B2B-XH-A_1x02_P2.50mm_Vertical
J5: USB-C (bench flash only); USB_C_Receptacle_HRO_TYPE-C-31-M-12
J6: S1_IN (steam probe plug); EXCON_2547-02_WV
J7: S1_OUT (to control board M2); EXCON_2547-02_WV
J8: S2+SB_IN (group probe + steam level plug); EXCON_2547-04_WV
J9: S2+SB_OUT (to control board M3); EXCON_2547-04_WV
J12: SL_IN (tank sensor plug); EXCON_2547-02_WV
J13: SL_OUT (to control board M10); EXCON_2547-02_WV
J14: ENC_IN (encoder cable plug); Molex_KK-254_AE-6410-04A_1x04_P2.54mm_Vertical
J15: ENC_OUT (to ito ENC); Molex_KK-254_AE-6410-04A_1x04_P2.54mm_Vertical
J16: Qwiic; JST_SH_SM04B-SRSS-TB_1x04-1MP_P1.00mm_Horizontal
J17: ito EXPANSION pads; PinHeader_1x05_P2.54mm_Vertical
J18: SER stub; PinHeader_1x06_P2.54mm_Vertical
J19: ON/OFF contact; PinHeader_1x02_P2.54mm_Vertical
J20: M9 RS232 tap (cable to control board M9); EXCON_2547-04_WV
J21: M9 link field; PinHeader_1x06_P2.54mm_Vertical
J22: M9 RS-232 link pads; PinHeader_1x02_P2.54mm_Vertical
JP2: EXP_SDA link; SolderJumper-2_P1.3mm_Open_RoundedPad1.0x1.5mm
JP3: EXP_SCL link; SolderJumper-2_P1.3mm_Open_RoundedPad1.0x1.5mm
Q1, Q2, Q3: AO3400A; SOT-23
R1, R2, R13, R14: 5.1k; R_0603_1608Metric
R3, R4, R9, R10, R21, R55: 10k; R_0603_1608Metric
R5, R6, R24, R25, R26, R27: 1M; R_0603_1608Metric
R22, R23, R31, R32, R33: 100k; R_0603_1608Metric
R28, R29, R30: 1k; R_0603_1608Metric
R34, R35, R37, R38: 4.7k; R_0603_1608Metric
R36: 200k; R_0603_1608Metric
R39, R52, R53, R54: 0; R_0603_1608Metric
R40, R41, R42, R43, R44, R45, R46, R47, R49, R50, R51: TBD; R_0603_1608Metric
R48: 330; R_0603_1608Metric
SW1: EN/RESET; SW_Push_1P1T_XKB_TS-1187A
SW2: BOOT (GPIO0); SW_Push_1P1T_XKB_TS-1187A
TP1: TXD0; TestPoint_Pad_D1.5mm
TP2: RXD0; TestPoint_Pad_D1.5mm
TP3: EN; TestPoint_Pad_D1.5mm
TP4: BOOT; TestPoint_Pad_D1.5mm
TP5: +3V3; TestPoint_Pad_D1.5mm
TP6: +5V; TestPoint_Pad_D1.5mm
TP7: GND; TestPoint_Pad_D1.5mm
U1, U2, U8, U9, U10: 74LVC1G17; SOT-23-5
U3: USBLC6-2SC6; SOT-23-6
U4: AMS1117-3.3; SOT-223-3_TabPin2
U5: ESP32-S3-WROOM-1-N8; ESP32-S3-WROOM-1
U6: MCP6004; SOIC-14_3.9x8.7mm_P1.27mm
U7: ADS1115; VSSOP-10_3x3mm_P0.5mm
U11: PCA9306; VSSOP-8_2.3x2mm_P0.5mm
U12: TLP222A; DIP-4_W7.62mm
U13: MAX3232; SOIC-16_3.9x9.9mm_P1.27mm

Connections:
+3V3: C2.1, C4.1, C5.1, C6.1, C13.1, C16.1, C17.1, C18.1, C23.1, D6.2, D7.2, D8.2, D9.2, D10.2, D11.2, D12.2, J16.2, R3.1, R4.1, R21.1, R24.1, R25.1, R34.1, R35.1, R39.1, R55.1, TP5.1, U2.5, U4.2, U5.2, U7.8, U8.5, U9.5, U10.5, U11.2, U13.16
+5V: C3.1, C8.1, D1.1, D2.2, D3.2, J4.1, TP6.1, U4.3, U6.4
ADS_ALERT: R21.2, U5.18, U7.2
BOOT: R4.2, SW2.1, TP4.1, U5.27
CC1: J5.A5, R1.1
CC2: J5.B5, R2.1
EN: C7.1, R3.2, SW1.1, TP3.1, U5.3
ENC_A: J14.3, J15.3, Q1.3, U8.2
ENC_B: J14.4, J15.4, Q2.3, U9.2
ENC_G_A: Q1.1, R28.2, R31.1
ENC_G_B: Q2.1, R29.2, R32.1
ENC_G_SW: Q3.1, R30.2, R33.1
ENC_INJ_A: R28.1, U5.4
ENC_INJ_B: R29.1, U5.5
ENC_INJ_SW: R30.1, U5.6
ENC_RD_A: U5.7, U8.4
ENC_RD_B: U5.8, U9.4
ENC_RD_SW: U5.9, U10.4
ENC_SW: J14.2, J15.2, Q3.3, U10.2
EXP_SCL: J17.4, JP3.2
EXP_SCL_T: JP3.1, R38.1, U11.6
EXP_SDA: J17.5, JP2.2
EXP_SDA_T: JP2.1, R37.1, U11.5
EXP_VREF2: R36.1, U11.7, U11.8
FLOW_3V3: U2.4, U5.19
GND: C1.2, C2.2, C3.2, C4.2, C5.2, C6.2, C7.2, C8.2, C9.2, C10.2, C13.2, C16.2, C17.2, C18.2, C21.2, C22.1, C23.2, D2.1, D3.1, D6.1, D7.1, D8.1, D9.1, D10.1, D11.1, D12.1, J1.3, J2.3, J3.1, J4.2, J5.A1, J5.A12, J5.B1, J5.B12, J5.S1, J6.1, J7.1, J8.1, J9.1, J15.1, J16.1, J16.MP, J17.2, J18.1, Q1.2, Q2.2, Q3.2, R1.2, R2.2, R13.2, R14.2, R26.2, R27.2, R31.2, R32.2, R33.2, R44.2, R45.2, R46.2, R47.2, R51.2, SW1.2, SW2.2, TP7.1, U1.3, U2.3, U3.2, U4.1, U5.1, U5.40, U5.41, U6.10, U6.11, U6.12, U7.1, U7.3, U7.6, U7.7, U8.3, U9.3, U10.3, U11.1, U12.2, U13.10, U13.15
I2C_SCL: J16.4, R35.2, U5.17, U7.10, U11.3
I2C_SDA: J16.3, R34.2, U5.12, U7.9, U11.4
ITO_EXP_5V: J17.1, R36.2, R37.2, R38.2
M9_P1: J20.1, J21.1
M9_P2: J20.2, J21.2
M9_P3: J20.3, J21.3
M9_P4: J20.4, J21.4
M9_RX: D12.3, R50.2, R51.1, R54.2, U5.31
M9_RX_H: J21.6, R50.1
M9_TX: R49.1, R55.2, U5.23, U13.11
M9_TX_H: J21.5, R49.2
MAX_C1N: C19.2, U13.3
MAX_C1P: C19.1, U13.1
MAX_C2N: C20.2, U13.5
MAX_C2P: C20.1, U13.4
MAX_VN: C22.2, U13.6
MAX_VP: C21.1, U13.2
N_O: J1.4, J2.4, U1.2, U2.2
N_OUT: J3.2, U1.4
N_PLUS: J1.2, J2.2
ONOFF_C1: J19.1, U12.4
ONOFF_C2: J19.2, U12.3
ONOFF_DRV: R48.1, U5.20
ONOFF_LED: R48.2, U12.1
RS_DOUT1: R52.1, U13.14
RS_RIN1: R53.2, U13.13
RS_ROUT1: R54.1, U13.12
RS_RX_H: J22.2, R53.1
RS_TX_H: J22.1, R52.2
S1_ADC: C9.1, R9.2, R13.1, U7.4
S1_BUF: R9.1, U6.1, U6.2
S1_FEED: J6.2, J7.2, R5.1
S1_IN: D2.3, R5.2, U6.3
S2_ADC: C10.1, R10.2, R14.1, U7.5
S2_BUF: R10.1, U6.6, U6.7
S2_FEED: J8.2, J9.2, R6.1
S2_IN: D3.3, R6.2, U6.5
SB_AC: C14.2, R22.1
SB_AUX: J8.4, J9.4
SB_FE: D6.3, R22.2, R24.2, R26.1, U5.39
SB_PROBE: C14.1, J8.3, J9.3
SER_3V3_H: J18.2, R39.2
SER_IO1: D10.3, R42.2, R46.1, U5.21
SER_IO1_H: J18.5, R42.1
SER_IO2: D11.3, R43.2, R47.1, U5.22
SER_IO2_H: J18.6, R43.1
SER_RX: D9.3, R41.2, R45.1, U5.11
SER_RX_H: J18.4, R41.1
SER_TX: D8.3, R40.2, R44.1, U5.10
SER_TX_H: J18.3, R40.1
SL_AC: C15.2, R23.1
SL_AUX: J12.2, J13.2
SL_FE: D7.3, R23.2, R25.2, R27.1, U5.38
SL_PROBE: C15.1, J12.1, J13.1
U0RXD: TP2.1, U5.36
U0TXD: TP1.1, U5.37
U6C_FB: U6.8, U6.9
U6D_FB: U6.13, U6.14
USB_DN: J5.A7, J5.B7, U3.3, U3.4, U5.13
USB_DP: J5.A6, J5.B6, U3.1, U3.6, U5.14
V5_ITO: C1.1, J3.3, U1.5
VBUS: D1.2, J5.A4, J5.A9, J5.B4, J5.B9, U3.5

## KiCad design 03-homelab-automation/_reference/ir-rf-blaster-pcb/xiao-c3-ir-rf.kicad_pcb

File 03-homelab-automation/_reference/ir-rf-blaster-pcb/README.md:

# XIAO ESP32-C3 IR + RF blaster hat — KiCad project

A XIAO-carrier "hat": the XIAO ESP32-C3 sockets in horizontally (USB-C off the **west** edge), the
board carries a **triple-940 nm IR blaster** (MOSFET-driven) on the front, and an **E07-M1101D
(CC1101) sub-GHz module** rides a swappable 2×4 female socket flipped to the **back** with its
antenna off the **south** edge. Design rationale + build lifecycle are in the project doc:
[03-027](../../03-027-xiao-c3-ir-rf-blaster-carrier-pcb.md).

**Status (2026-07-14): routed + DRC-clean, fab-ready.** Generated headlessly (`generate_pcb.py`,
kiutils), zone-filled (`fill.py`, pcbnew), validated with `kicad-cli` (DRC: **0 violations, 0
unconnected**). Gerbers/drill are in [`xiao-c3-ir-rf-gerbers.zip`](xiao-c3-ir-rf-gerbers.zip);
renders are [`…-top.png`](xiao-c3-ir-rf-top.png) / [`…-bottom.png`](xiao-c3-ir-rf-bottom.png). Board
size **23 × 54 mm**, **4-layer**.

> Open `xiao-c3-ir-rf.kicad_pcb` in KiCad for a final eyeball before ordering. The E07 socket is on
> the back so the module tucks over the XIAO; confirm the module body clears the XIAO's USB-C shell.

## Stackup (4-layer)

| Layer    | Use                                             |
| -------- | ----------------------------------------------- |
| `F.Cu`   | parts + signal (IR front-end, XIAO fan-out)     |
| `In1.Cu` | **GND** plane                                   |
| `In2.Cu` | **+5 V** plane                                  |
| `B.Cu`   | signal + the E07 module socket (module on back) |

Every SMD GND pad stitches to `In1` and every SMD +5 V pad to `In2` with a via; the XIAO's power
pins are through-hole so they hit the planes directly.

## Floorplan (north → south)

1. **IR LEDs** (D1–D3, 940 nm THT 5 mm) across the north edge, aimed off-board.
2. **Current-limit R** (R1–R3, 15 Ω) then the **MOSFET gate cluster** (Q1 + R4/R5, C1/C2 bulk).
3. **XIAO ESP32-C3** (official Seeed DIP footprint, rotated 180° → USB-C exits the **west** edge).
4. **E07-M1101D** on a 2×4 female socket, flipped to the **back**, antenna off the **south** edge,
   with its 3V3 decaps (C3/C4) in the strip below the XIAO.

## Pin map (XIAO C3 — no strapping pins used)

| Net       | XIAO pin | GPIO | Use                                           |
| --------- | -------- | ---- | --------------------------------------------- |
| `IR_TX`   | D1       | 3    | MOSFET gate drive (IR LEDs)                   |
| `CC_CSN`  | D2       | 4    | CC1101 chip-select                            |
| `CC_MOSI` | D3       | 5    | SPI MOSI                                      |
| `CC_GDO2` | D4       | 6    | CC1101 aux (optional)                         |
| `CC_MISO` | D6       | 21   | SPI MISO                                      |
| `CC_SCK`  | D7       | 20   | SPI clock                                     |
| `CC_GDO0` | D10      | 10   | CC1101 OOK data (`remote_transmitter` drives) |

Strapping pins **D0/GPIO2, D8/GPIO8, D9/GPIO9** are left spare. `IR_TX` is on **D1/GPIO3** (not D0)
so the 10 kΩ gate pulldown can't drag a strap low at reset. **Power:** XIAO 3V3 → module VCC; **+5 V
(VBUS)** → IR LEDs; common GND.

> ⚠ **Firmware must match this pin map.** The ESPHome config
> (`gjcourt/homelab → firmware/esphome/ir-rf-blaster-xiao-c3.yaml`) predates this re-layout and used
> the older v0.2 assignment — align its GPIOs to the table above before flashing.

## Components

| Ref     | Value / Part                   | Footprint                         | Notes                              |
| ------- | ------------------------------ | --------------------------------- | ---------------------------------- |
| D1–D3   | 940 nm IR LED (e.g. TSAL6400)  | `LED_D5.0mm`                      | THT, hand-solder; D3 optional/DNP  |
| R1–R3   | 15 Ω                           | `R_0805_2012Metric`               | LED current limit. JLC SMT (Basic) |
| Q1      | **AO3400A** N-ch MOSFET        | `SOT-23`                          | low-side switch. JLC SMT           |
| R4      | 100 Ω                          | `R_0603_1608Metric`               | gate series. JLC SMT               |
| R5      | 10 kΩ                          | `R_0603_1608Metric`               | gate pulldown → GND. JLC SMT       |
| C1 / C2 | 100 nF / 22 µF                 | `C_0603` / `C_0805`               | 5 V decouple + bulk. JLC SMT       |
| C3 / C4 | 100 nF / 10 µF                 | `C_0603` / `C_0805`               | 3V3 decouple at module. JLC SMT    |
| A1      | **XIAO ESP32-C3**              | `XIAO-ESP32-C3-DIP`               | socketed (2×7 female headers)      |
| M1      | **E07-M1101D** (CC1101 module) | `PinSocket_2x04_P2.54mm_Vertical` | **back-mounted, swappable**        |

`M1` socket is on the **back** so the module is removable — swap E07 bands (315/433/868/915 MHz)
without re-spinning the board. E07-M1101D pinout (CDEBYTE fixed): **1 GND · 2 VCC(3V3) · 3 GDO0 · 4
CSN · 5 SCK · 6 MOSI · 7 MISO · 8 GDO2**.

## Regenerate / validate / fab (headless)

```sh
# 1. generate the board (native, no KiCad needed) — writes UNFILLED zones
python3 generate_pcb.py footprints xiao-c3-ir-rf.kicad_pcb

# 2. fill zones + validate + export with kicad-cli (KiCad 9; on Apple Silicon use the amd64 image)
docker run --rm --platform linux/amd64 -v "$PWD:/w" -w /w kicad/kicad:9.0 sh -c '
  python3 fill.py xiao-c3-ir-rf.kicad_pcb xiao-c3-ir-rf.kicad_pcb
  kicad-cli pcb drc xiao-c3-ir-rf.kicad_pcb
  kicad-cli pcb export gerbers -o gerbers/ xiao-c3-ir-rf.kicad_pcb
  kicad-cli pcb export drill   -o gerbers/ xiao-c3-ir-rf.kicad_pcb
  kicad-cli pcb export svg --layers "F.Cu,Edge.Cuts,F.Silkscreen" --page-size-mode 2 -o top.svg xiao-c3-ir-rf.kicad_pcb'
```

`footprints/` holds the eight KiCad footprints the generator places (so it runs without a local
KiCad install). `fill.py` zone-fills via `pcbnew.ZONE_FILLER` — needed because the planes are
written unfilled.

> Note: `pcbnew`'s `FootprintLoad` crashes under amd64 emulation on Apple Silicon, so the board is
> **generated** with kiutils (pure Python, native) and only the compiled `kicad-cli` / `pcbnew`
> zone-filler run in the container.

## Order (JLC)

1. Upload [`xiao-c3-ir-rf-gerbers.zip`](xiao-c3-ir-rf-gerbers.zip). Select **4-layer**.
2. Enable **SMT assembly** (top side only) and upload the BOM + CPL:
   - BOM: [`xiao-c3-ir-rf-BOM.csv`](xiao-c3-ir-rf-BOM.csv)
   - CPL / pick-and-place: [`xiao-c3-ir-rf-CPL.csv`](xiao-c3-ir-rf-CPL.csv)
3. Hand-solder the 3 IR LEDs (`D1–D3`), the XIAO sockets (`A1`), and the E07 socket (`M1`) — they're
   not in the BOM/CPL.
4. The E07 module drops into its 2×4 socket on the back — leave it removable for band swaps.

### Assembly BOM (all JLC **Basic** — no extended-part fee)

| Designator | Value   | Package | LCSC   | Library |
| ---------- | ------- | ------- | ------ | ------- |
| R1,R2,R3   | 15 Ω    | 0805    | C17480 | Basic   |
| R4         | 100 Ω   | 0603    | C22775 | Basic   |
| R5         | 10 kΩ   | 0603    | C25804 | Basic   |
| C1,C3      | 100 nF  | 0603    | C14663 | Basic   |
| C2         | 22 µF   | 0805    | C45783 | Basic   |
| C4         | 10 µF   | 0805    | C15850 | Basic   |
| Q1         | AO3400A | SOT-23  | C20917 | Basic   |

> ⚠ **Verify rotations in JLC's CPL preview before ordering.** The CPL carries KiCad's rotations;
> chip R/C usually map 1:1, but **`Q1` (SOT-23) commonly needs a 180° flip** to line pin 1 up with
> JLC's part orientation. JLC's online viewer overlays each part on its footprint — spin any that
> look wrong there (it's non-destructive, and easier than second-guessing the CSV).

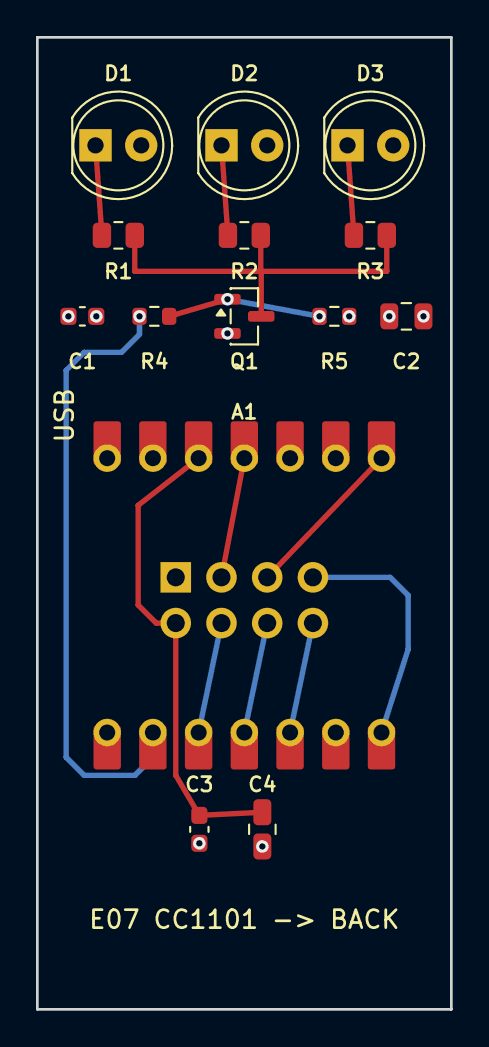
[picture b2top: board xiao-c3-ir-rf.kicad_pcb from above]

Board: 4 copper layers, 23.0 x 54.0 mm, 15 parts (1 on the bottom side), 15 nets.

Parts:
A1: XIAO_ESP32C3; XIAO-ESP32-C3-DIP
C1, C3: 100nF; C_0603_1608Metric
C2: 22uF; C_0805_2012Metric
C4: 10uF; C_0805_2012Metric
D1, D2, D3: 940nm; LED_D5.0mm
M1: E07-M1101D; PinSocket_2x04_P2.54mm_Vertical
Q1: AO3400A; SOT-23
R1, R2, R3: 15R; R_0805_2012Metric
R4: 100R; R_0603_1608Metric
R5: 10k; R_0603_1608Metric

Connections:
+3V3: A1.12, C3.1, C4.1, M1.2
+5V: A1.14, C1.1, C2.1, D1.2, D2.2, D3.2
CC_CSN: A1.3, M1.4
CC_GDO0: A1.11, M1.3
CC_GDO2: A1.5, M1.8
CC_MISO: A1.7, M1.7
CC_MOSI: A1.4, M1.6
CC_SCK: A1.8, M1.5
GND: A1.13, C1.2, C2.2, C3.2, C4.2, M1.1, Q1.2, R5.2
IR_TX: A1.2, R4.1
LED1_K: D1.1, R1.1
LED2_K: D2.1, R2.1
LED3_K: D3.1, R3.1
Q_DRAIN: Q1.3, R1.2, R2.2, R3.2
Q_GATE: Q1.1, R4.2, R5.1

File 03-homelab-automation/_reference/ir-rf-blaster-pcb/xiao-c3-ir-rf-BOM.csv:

Comment,Designator,Footprint,LCSC Part #
15R,"R1,R2,R3",R_0805_2012Metric,C17480
100R,R4,R_0603_1608Metric,C22775
10k,R5,R_0603_1608Metric,C25804
100nF,"C1,C3",C_0603_1608Metric,C14663
22uF,C2,C_0805_2012Metric,C45783
10uF,C4,C_0805_2012Metric,C15850
AO3400A,Q1,SOT-23,C20917

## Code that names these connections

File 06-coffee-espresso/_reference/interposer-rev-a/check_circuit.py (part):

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        ref = split(pin)[0]
        if ref != owner and ref not in dnp_refs:
            probs.append(f'{net}: {pin} is fitted; only DNP links may join {owner} here')
for pin in ckt.NETS['M9_P1'] + ckt.NETS['M9_P2'] + ckt.NETS['M9_P3'] + ckt.NETS['M9_P4']:
    if split(pin)[0] not in dnp_refs:
        probs.append(f'{pin} is fitted on an M9 line')
if pin_net.get('U13.11') != ['M9_TX'] or not any(split(p)[0] == 'R55' for p in ckt.NETS['M9_TX']):
    probs.append('U13 DIN1 must be on M9_TX with the R55 pull-up (SLLS410O §9.2.2)')
check('C11', 'M9 tap: machine side reached only through DNP links', probs)

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
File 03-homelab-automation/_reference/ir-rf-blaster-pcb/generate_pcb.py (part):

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setnet(C1, 1, "+5V"); setnet(C1, 2, "GND"); setnet(C2, 1, "+5V"); setnet(C2, 2, "GND")
setnet(C3, 1, "+3V3"); setnet(C3, 2, "GND"); setnet(C4, 1, "+3V3"); setnet(C4, 2, "GND")
# E07-M1101D FIXED CDEBYTE pinout: 1 GND 2 VCC(3V3) 3 GDO0 4 CSN 5 SCK 6 MOSI 7 MISO 8 GDO2
for pin, net in [(1,"GND"),(2,"+3V3"),(3,"CC_GDO0"),(4,"CC_CSN"),(5,"CC_SCK"),
                 (6,"CC_MOSI"),(7,"CC_MISO"),(8,"CC_GDO2")]:
    setnet(M1, pin, net)
# XIAO official pad map (pad#=signal): 1 D0, 2 D1, 3 D2, 4 D3, 5 D4, 6 D5, 7 D6, 8 D7, 9 D8,
#   10 D9, 11 D10, 12 3V3, 13 GND, 14 5V(VBUS). Strapping pins = D0/D8/D9 (pads 1/9/10) are ALL
#   left spare: IR_TX is on D1/GPIO3 (non-strapping). D0 avoided because the 10k gate pulldown
#   would drag GPIO2 low at reset (~0.6V via the ~45k internal pull-up), against ESP32-C3 guidance.
XIAO = {2:"IR_TX", 3:"CC_CSN", 4:"CC_MOSI", 5:"CC_GDO2", 7:"CC_MISO", 8:"CC_SCK",
        11:"CC_GDO0", 12:"+3V3", 13:"GND", 14:"+5V"}
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route([g, r51], "Q_GATE", "B.Cu")                                 # gate -> R5 (B.Cu, clears drain)
# IR_TX: XIAO D1 (south-west) up the west edge, in along y17.5 (south of the driver row and
# clear of C1's GND via), then up into R4.1 (B.Cu)
r41 = abspad(R4, 1); d1 = abspad(A1, 2)   # IR_TX on D1/GPIO3 (non-strapping)
# drop south of the XIAO pad row first (clears the spare D0 pad) then up the west edge to R4
route([d1, (d1[0], 41.0), (1.6, 41.0), (1.6, 17.5), (r41[0], 17.5), r41], "IR_TX", "B.Cu")
via(r41, "IR_TX")                                                 # B.Cu IR_TX -> F.Cu R4.1 pad
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
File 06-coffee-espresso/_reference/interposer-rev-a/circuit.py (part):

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    18: ('SER_RX', 'in', 'U1RXD default (F8 stub, DNP)'),
    19: ('USB_DN', 'usb', 'USB_D- (fixed function)'),
    20: ('USB_DP', 'usb', 'USB_D+ (fixed function)'),
    21: ('M9_TX', 'out', 'UART2 TX via the GPIO matrix: U13 DIN1 + R55 pull-up; passive R49 (DNP)'),
    38: ('M9_RX', 'in', 'UART2 RX via the GPIO matrix: U13 ROUT1 via R54 or passive R50 (both DNP links)'),
}

# Rules the checker enforces (module datasheet v1.8 §3 Table 3-1 notes, §4 Table 4-1):
STRAPPING_GPIO = {0, 3, 45, 46}  # Table 4-1
OCTAL_PSRAM_GPIO = {35, 36, 37}  # Table 3-1 note b: used by octal PSRAM on R8/R16V variants
NOT_LED_OUT_GPIO = {22, 23, 24, 25, 26, 27, 28, 29, 30, 31, 32, 33, 34}  # absent from Table 3-1
USB_GPIO = {19: 'USB_DN', 20: 'USB_DP'}  # Table 3-1: IO19 = USB_D-, IO20 = USB_D+
UART0_GPIO = {43, 44}  # TXD0/RXD0: kept free for the ROM console
ADC1_GPIO = set(range(1, 11))  # GPIO1..10 = ADC1_CH0..9 (Table 3-1). ADC2 is unusable with Wi-Fi
ANALOG_NETS = {'SB_FE', 'SL_FE'}
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
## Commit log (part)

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2026-05-24 docs(06-011): include auto-shutoff solenoid in initial delivery
    Promote the NC brass solenoid valve from a reserved Phase-2 enhancement
    into the Phase-1 install. Adds BOM lines (valve, smart plug, coil
    supply), wiring guidance under the regulation-stack build, a functional
    power-cycle / power-loss exit-criterion, and a "hose-burst flood while
    unattended" failure-mode entry. Removes the now-obsolete out-of-scope
    deferral and the Phase-2 solenoid entry; leaves HA-software integration
